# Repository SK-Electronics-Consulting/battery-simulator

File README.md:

# Battery Simulator

When developing new hardware, engineers often need to see how the device will perform while running on battery power. 
Because it is not always convenient to use real batteries for testing, battery simulators have been developed. 
However, commercial battery simulators are expensive, sometimes costing well into the thousands of dollars. 
As an alternative, I have developed an open-source battery simulator that can be built in a home workshop for under $100. 

A battery simulator is a piece of text equipment which does exactly that, simulates a battery. 
The main difference between a battery simulator and a "general purpose" power supply is that the power supply will only source current at a positive voltage, while the battery simulator will both source and sink current also at a positive voltage. 
If you map this capability out to a [Cartesian Plane](https://en.wikipedia.org/wiki/Quadrant_(plane_geometry)), you can use the quadrants as a short-hand way of describing the capability of the device. 
A general purpose power supply (e.g. [Siglent SPD1000X](https://siglentna.com/power-supplies/spd1000x-series-programmable-dc-power-supply/)) is a 1-quadrant power supply because it can only source current and can only do positive voltage. 
A battery simulator like the [Keithley 2302](https://www.tek.com/en/datasheet-/model-2302-battery-simulator-models-2306-and-2306-pj-battery-chargers-simulato) is a 2-quadrant supply because it operates only at a positive voltage, but can source (positive) or sink (negative) current. 
An example of a 4-quadrant power supply would be an SMU (Source Measure Unit) like the [Keithley 2400](https://www.tek.com/en/products/keithley/source-measure-units/2400-graphical-series-sourcemeter). 

> NOTE: Terms like battery simulator, SMU, and power supply may imply a certain number of quadrants, but unfortunately it is not guaranteed.  Always check the datasheet to make sure it's not a marketing term.  

The goal of this project is to make an open-source, lowish-cost battery simulator. This is both to give people access to using devices like this, but also as a design exercise in analog design.  

# Requirements
1. Device shall simulate a single cell Lithium Ion battery, so a voltage of 2.0 V - 4.4 V
1. Device shall have a current output of 1A, both sourcing and sinking.
1. Device shall be powered by an external power supply. 

# Phases
## Phase 1
Create a circuit that will operate as a 2-quadrant power supply.  This might be as simple as using a high-power output op-amp and a potentiometer. 

* TODO: Check if the op-amp will sink current in addition to sourcing. 

### Design Output

The [OPA569](https://www.ti.com/lit/ds/symlink/opa569.pdf) was selected as an available (yaaay chip shortage!) high power op-amp. 
It has some nifty features that are on the [wishlist](#future-phase-wishlist) while satisfying the basic needs of this phase. 
It has a 2A output, along with a 300mV drop-out at 2A. This means that assuming a 5V source (USB or the like), it can maintain it's output at 4.7V, which is well above the 4.2-4.4V max needed simulating 1S Lithium cells. 
This chip does leave some room for improvement.  It has a surprisingly high quiescent current, especially one that varies with current limit.  

### Limitations of Phase 1

* The OPA569 has a max voltage of 5.5V, so only 1S Lithium batteries will be doable.
* Current Monitor pin can only indicate sourcing current.  This could be fixed a couple ways, but is going to stay out of scope for this phase. 

## Future Phase Wishlist

These are features that will be added in future versions.  The list is roughly in order of priority.  

1. USB-C Power Supply
1. Current Monitor Output (Analog to a scope.  Need to define bandwidth required)
1. A good UI (MCU + screen + knob/buttons?)
1. Adding ESR to the current path.  
1. Programmability for adding smarts.  
    1. Voltage limits based on chemistry.  (e.g. 0.5-1.5V for Alkaline, 2.0-4.4V for Lithium-Ion, 1.0-1.2V for NiMH)
    1. Ability to simulate actual charging and discharging based on pre-made curves and a user-defined capacity
1. Considering moving away from an op-amp design, and moving towards a more bespoke and power efficient design.  
1. It might be cool to add "between cells" taps to allow multi-cell chargers who do cell balancing to operate correctly. 

# Out of scope

1. At the moment, this device will not have a way to be adjusted for the sake of calibration.  Not to say this is impossible, but for an open-source, low-cost project, this is unnecessary.
1. This device will never have a need for [4 quadrant operation](https://edadocs.software.keysight.com/kkbopen/what-is-a-bipolar-four-quadrant-power-supply-583425137.html)

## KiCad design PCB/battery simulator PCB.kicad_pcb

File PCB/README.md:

# battery simulator PCB

[Replace these texts and sections as needed.  This file should desribe the PCB, and associated information.]

## Background

[Fill this out with general info]

## [Next Section]

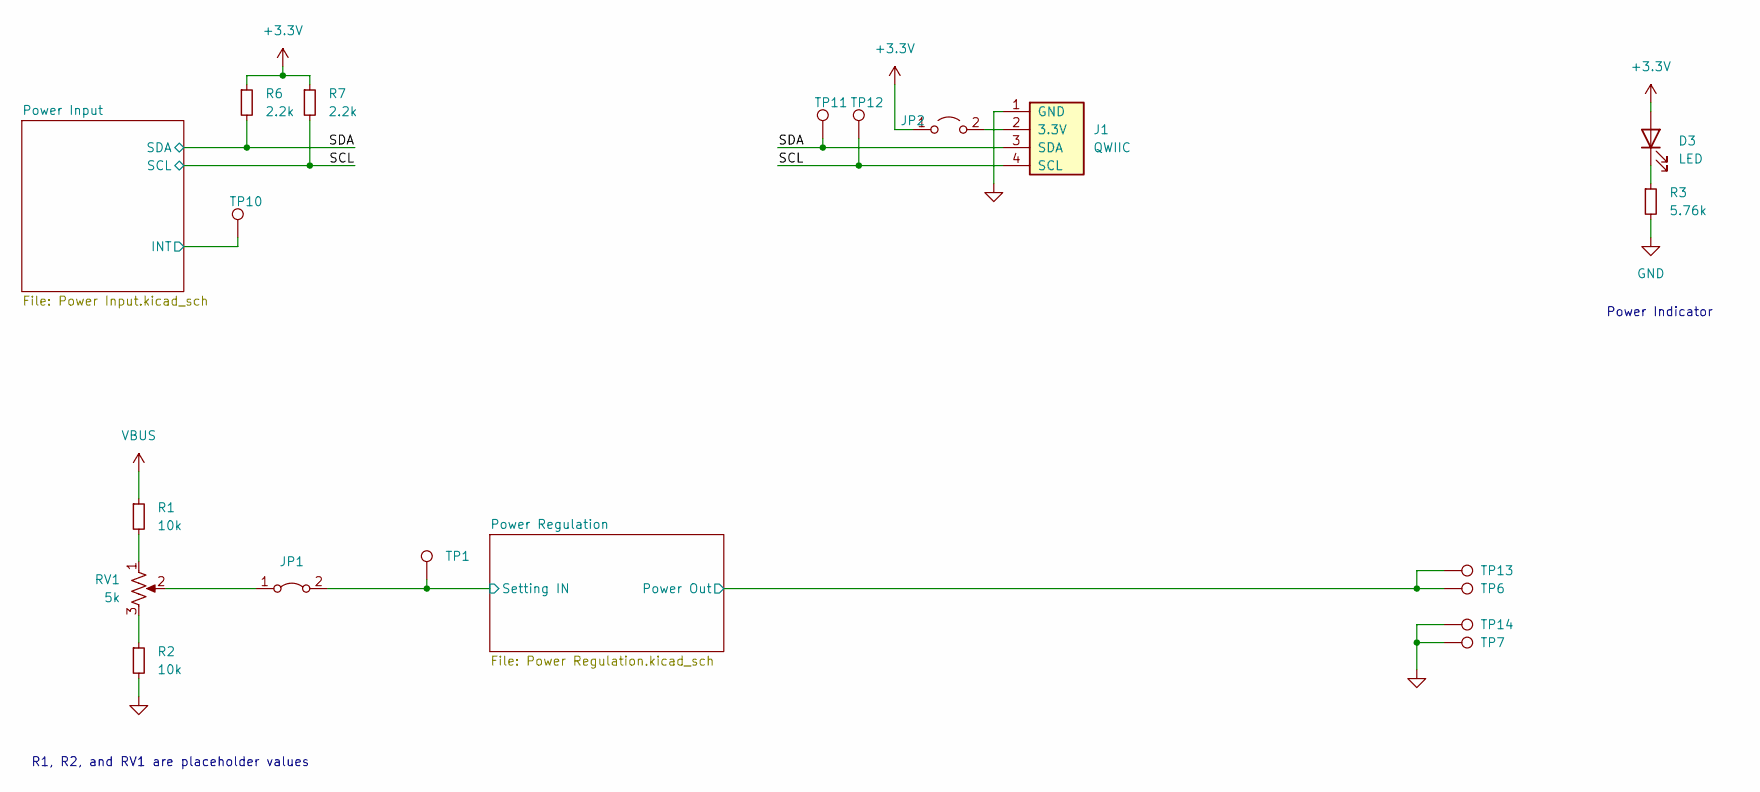
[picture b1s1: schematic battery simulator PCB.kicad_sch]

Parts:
D3: LED; LED_0603_1608Metric_Pad1.05x0.95mm_HandSolder
J1: QWIIC; JST_SH_SM04B-SRSS-TB_1x04-1MP_P1.00mm_Horizontal
JP1: Jumper_2_Bridged; SolderJumper-2_P1.3mm_Bridged_RoundedPad1.0x1.5mm
JP2: Jumper_2_Open; PinHeader_1x02_P2.54mm_Vertical
R1, R2: 10k; R_0402_1005Metric_Pad0.72x0.64mm_HandSolder
R3: 5.76k; R_0402_1005Metric_Pad0.72x0.64mm_HandSolder
R6, R7: 2.2k; R_0402_1005Metric_Pad0.72x0.64mm_HandSolder
RV1: 5k; Potentiometer_Bourns_3296W_Vertical
TP1, TP10, TP11, TP12: TestPoint; TestPoint_Keystone_5000-5004_Miniature
TP6, TP7, TP13, TP14: TestPoint; SolderWire-1sqmm_1x01_D1.4mm_OD2.7mm

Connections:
+3.3V: D3.2 (A), JP2.1 (A), R6.1, R7.1; also elsewhere on the board
/Power Input/INT: TP10.1; also elsewhere on the board
/Power Regulation/Power Out: TP6.1, TP13.1; also elsewhere on the board
/Power Regulation/Setting IN: JP1.2 (B), TP1.1; also elsewhere on the board
/SCL: J1.4 (SCL), R7.2, TP12.1; also elsewhere on the board
/SDA: J1.3 (SDA), R6.2, TP11.1; also elsewhere on the board
GND: J1.1 (GND), R2.2, R3.2, TP7.1, TP14.1; also elsewhere on the board
unnamed: D3.1 (K), R3.1
unnamed: J1.2 (3.3V), JP2.2 (B)
unnamed: JP1.1 (A), RV1.2
unnamed: R1.2, RV1.1
unnamed: R2.1, RV1.3
VBUS: R1.1; also elsewhere on the board

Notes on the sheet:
R1, R2, and RV1 are placeholder values
Power Indicator

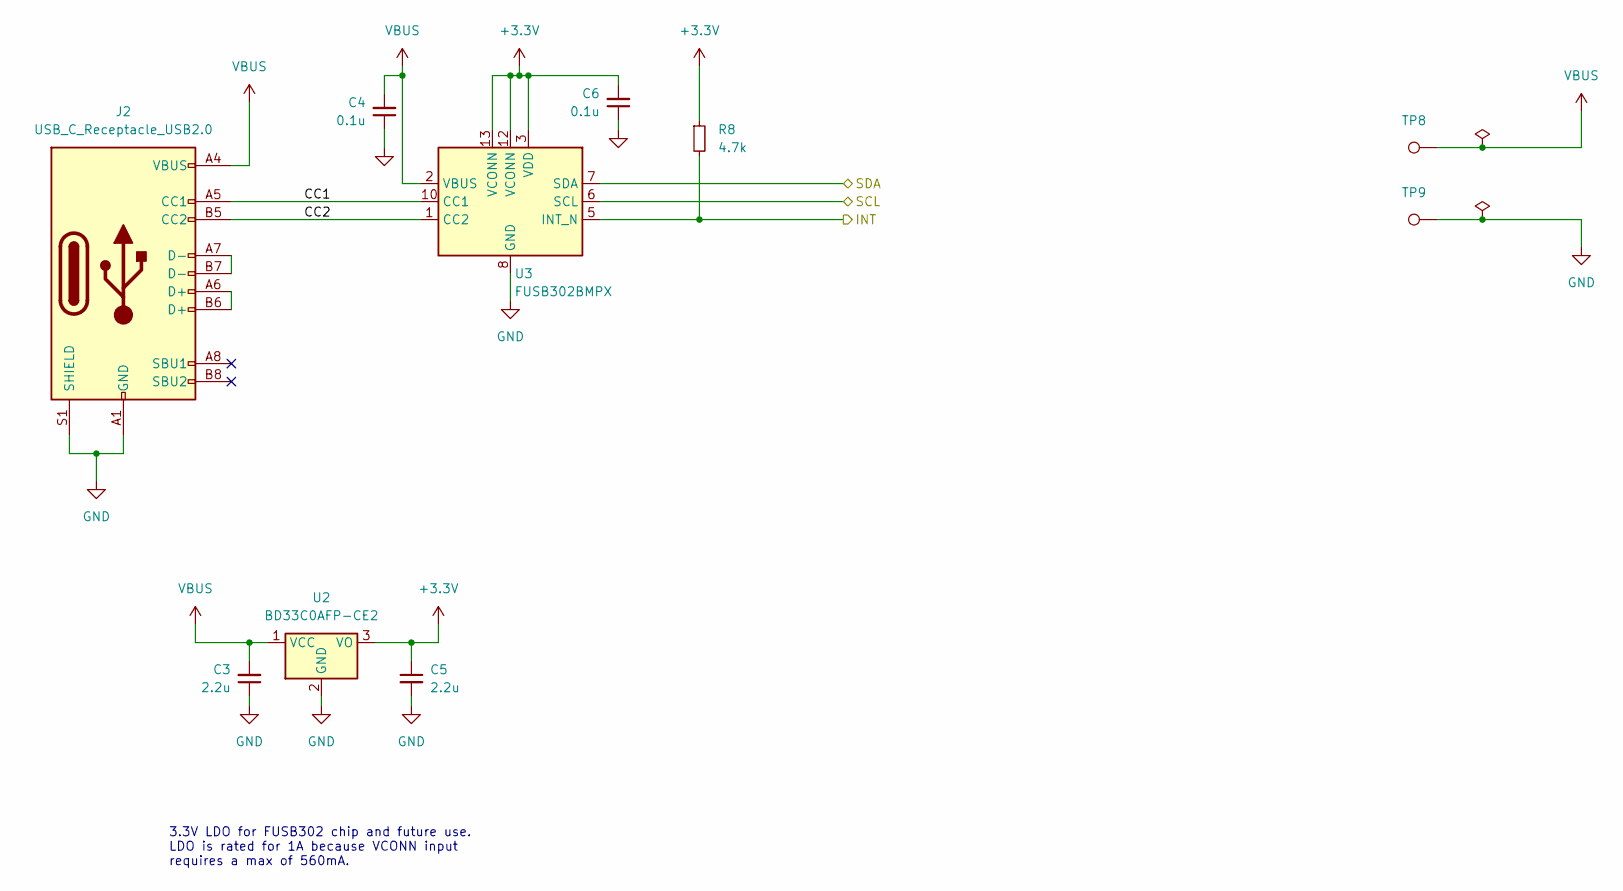
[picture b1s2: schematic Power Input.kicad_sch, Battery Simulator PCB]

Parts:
C3, C5: 2.2u; C_0805_2012Metric
C4, C6: 0.1u; C_0402_1005Metric_Pad0.74x0.62mm_HandSolder
J2: USB_C_Receptacle_USB2.0; USB_C_Receptacle_GCT_USB4085
R8: 4.7k; R_0402_1005Metric_Pad0.72x0.64mm_HandSolder
TP8, TP9: TestPoint; SolderWire-1sqmm_1x01_D1.4mm_OD2.7mm
U2: BD33C0AFP-CE2; TO-252-2
U3: FUSB302BMPX; WQFN-14-1EP_2.5x2.5mm_P0.5mm_EP1.45x1.45mm

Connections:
+3.3V: C5.1, C6.2, R8.1, U2.3 (VO), U3.3 (VDD), U3.4 (VDD), U3.12 (VCONN), U3.13 (VCONN); also elsewhere on the board
/Power Input/CC1: J2.A5 (CC1), U3.10 (CC1), U3.11 (CC1)
/Power Input/CC2: J2.B5 (CC2), U3.1 (CC2), U3.14 (CC2)
/Power Input/INT: R8.2, U3.5 (INT_N); also elsewhere on the board
/SCL: U3.6 (SCL); also elsewhere on the board
/SDA: U3.7 (SDA); also elsewhere on the board
GND: C3.1, C4.1, C5.2, C6.1, J2.A1 (GND), J2.A12 (GND), J2.B1 (GND), J2.B12 (GND), J2.S1 (SHIELD), TP9.1, U2.2 (GND), U3.8 (GND), U3.9 (GND), U3.15 (GND); also elsewhere on the board
unnamed: J2.A6 (D+), J2.B6 (D+)
unnamed: J2.A7 (D-), J2.B7 (D-)
VBUS: C3.2, C4.2, J2.A4 (VBUS), J2.A9 (VBUS), J2.B4 (VBUS), J2.B9 (VBUS), TP8.1, U2.1 (VCC), U3.2 (VBUS); also elsewhere on the board

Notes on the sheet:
3.3V LDO for FUSB302 chip and future use. LDO is rated for 1A because VCONN input requires a max of 560mA.

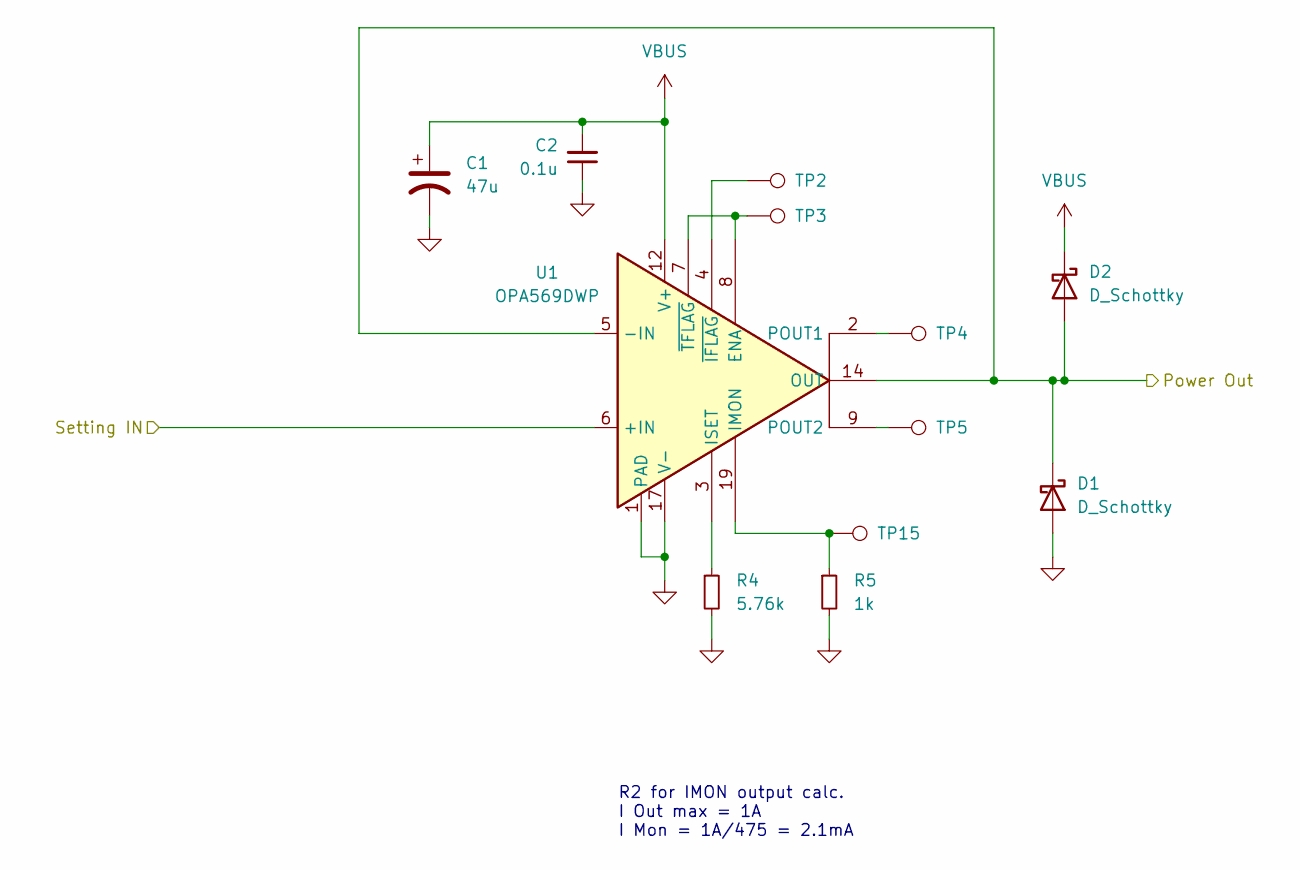
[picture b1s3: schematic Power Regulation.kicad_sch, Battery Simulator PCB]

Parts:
C1: 47u; CP_EIA-6032-20_AVX-F_Pad2.25x2.35mm_HandSolder
C2: 0.1u; C_0402_1005Metric_Pad0.74x0.62mm_HandSolder
D1, D2: D_Schottky; D_SMA-SMB_Universal_Handsoldering
R4: 5.76k; R_0402_1005Metric_Pad0.72x0.64mm_HandSolder
R5: 1k; R_0402_1005Metric_Pad0.72x0.64mm_HandSolder
TP2, TP3, TP4, TP5, TP15: TestPoint; TestPoint_Keystone_5000-5004_Miniature
U1: OPA569DWP; SO-20-1EP_7.52x12.825mm_P1.27mm_EP6.045x12.09mm_Mask3.56x4.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

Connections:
/Power Regulation/Power Out: D1.1 (K), D2.2 (A), U1.5 (-IN), U1.14 (OUT), U1.15 (OUT); also elsewhere on the board
/Power Regulation/Setting IN: U1.6 (+IN); also elsewhere on the board
GND: C1.2, C2.1, D1.2 (A), R4.2, R5.2, U1.1 (PAD), U1.10 (PAD), U1.11 (PAD), U1.17 (V-), U1.18 (V-), U1.20 (PAD), U1.21 (PAD); also elsewhere on the board
unnamed: TP3.1, U1.7 (~TFLAG), U1.8 (ENA)
unnamed: R5.1, TP15.1, U1.19 (IMON)
unnamed: R4.1, U1.3 (ISET)
unnamed: TP4.1, U1.2 (POUT1)
unnamed: TP5.1, U1.9 (POUT2)
unnamed: TP2.1, U1.4 (~IFLAG)
VBUS: C1.1, C2.2, D2.1 (K), U1.12 (V+), U1.13 (V+); also elsewhere on the board

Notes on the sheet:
R2 for IMON output calc. I Out max = 1A I Mon = 1A/475 = 2.1mA

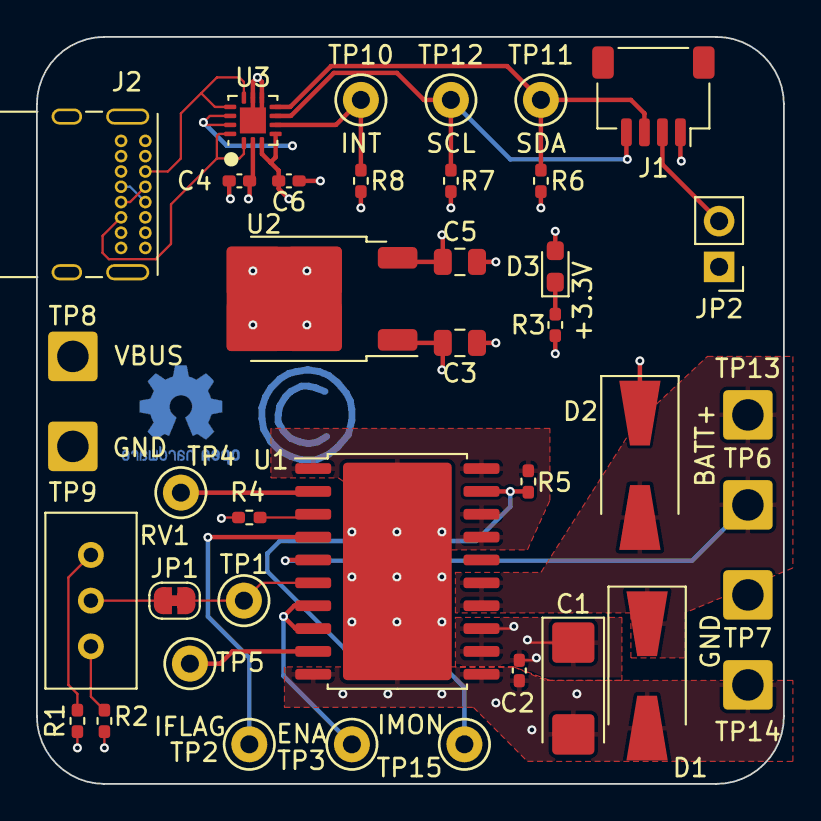
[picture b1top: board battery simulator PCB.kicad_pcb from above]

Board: 4 copper layers, 41.5 x 41.5 mm, 40 parts (0 on the bottom side), 23 nets.

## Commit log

2022-12-22 Update README with a general project plan, and gitignore.
    Updated the README with a general project plan. Also added
    phases section along with future improvements.
    Updated gitignore with KiCAD v6 info.
2022-12-22 Updated README with basic requirements.
2022-12-27 Completed op-amp circuit and basic power. Also updated README.
    Picked the op-amp and implemented that into the schematic.
    Selected basic placeholder components for power input and output.
    Updated README with relevant info.
    TODO: Consider going straight for USB power source.
    TODO: PCB Layout.
2023-01-01 Updated README.md with more info and some formating changes.
    Updated README with more info about battery simulators, some
    details, and other formatting.
    Thanks to @emilyvelasco for the edits and suggestions.
2023-01-14 Added FUSB302B and associated circuitry.
    Added FUSB302B, along with USB-C Connector and LDO. The LDO is
    needed to power the FUSB302B from the cable.
    Also added some debugging and convenience items such as a QWIIC
    connector and some test points.
2023-01-14 Imported and placed all components into PCB.
    Imported all components into PCB. Finalized PCB outline to 50mm x
    50mm square. Arranged all components into reasonable locations
    and added 2 planes.
    Schematic update is just adding netlabels to the CC1 and CC2 nets.
2023-05-12 Update to KiCAD v7, and finalize for V1 build
    Updated to KiCAD v7, which touched many files.
    Also made some changes to finalize board for prototype build. Simplified the
    circuit a bit to just something built and tested.
